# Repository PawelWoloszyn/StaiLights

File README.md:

Stairs is electronics and programming project of controlling stair lights (led strips attached to bottom side of each step) using arduino nano and tlc5940.
Project contains both electronic schematics and code needed to create such controller, mind that I'm neither professional electronics
circuit designer nor software developer therefore both code and schematics might be adjusted to benefit your own implication.

Right now the device is under development and will remain in this state until implemented in real which is going to allow it's
long term testing and proof it's reliability. In this moment it only serves presentation purpose.

How does it work???
Arduino Nano controlls two TLC5940 controllers which are basicaly 16 channel PWM controller (each chip). PWM signal is inverted and used to drive MOSFET tranzistors which are responsible for regulating the current running through led strips. In order to automate this device DS1307 RTC is used. Thanks to this, device will only be switched on within specified period of time which is calculated by Dusk2Dawn library, lights are triggered by two PIR sensors one upstairs and one downstairs but there are plenty enough spare pins on Arduino nano to use other type of sesnor. Project also allows to externaly regulate device's parameters using microswitch buttons and potentiometer. 

Questions that might bother you:

* What do you need for logical inverters?
- TLC5940 cannot be connected directly to MOSFETS in this project due to it's 0 based logic, of course they could be driven with inverted logic but because of the way tlc functions, you wouldn't be able to completely shut down the lights.

* On schematic you started connecting TLC pins starting from output 2 not 0 why?
- It's because I bought one chip from second hand with one pin missing. Therefore I skipped pin0 and pin1(missing).

Future improvements:
* Definitely chaging DS1307 to DS3231 in order to gain benefits of having alarm clock function in real time clock, which could later on be used to     wake up arduino from sleep mode.
* Reworking board design to decrease it's dimensions, would probably make a 2 sided SMD PCB.

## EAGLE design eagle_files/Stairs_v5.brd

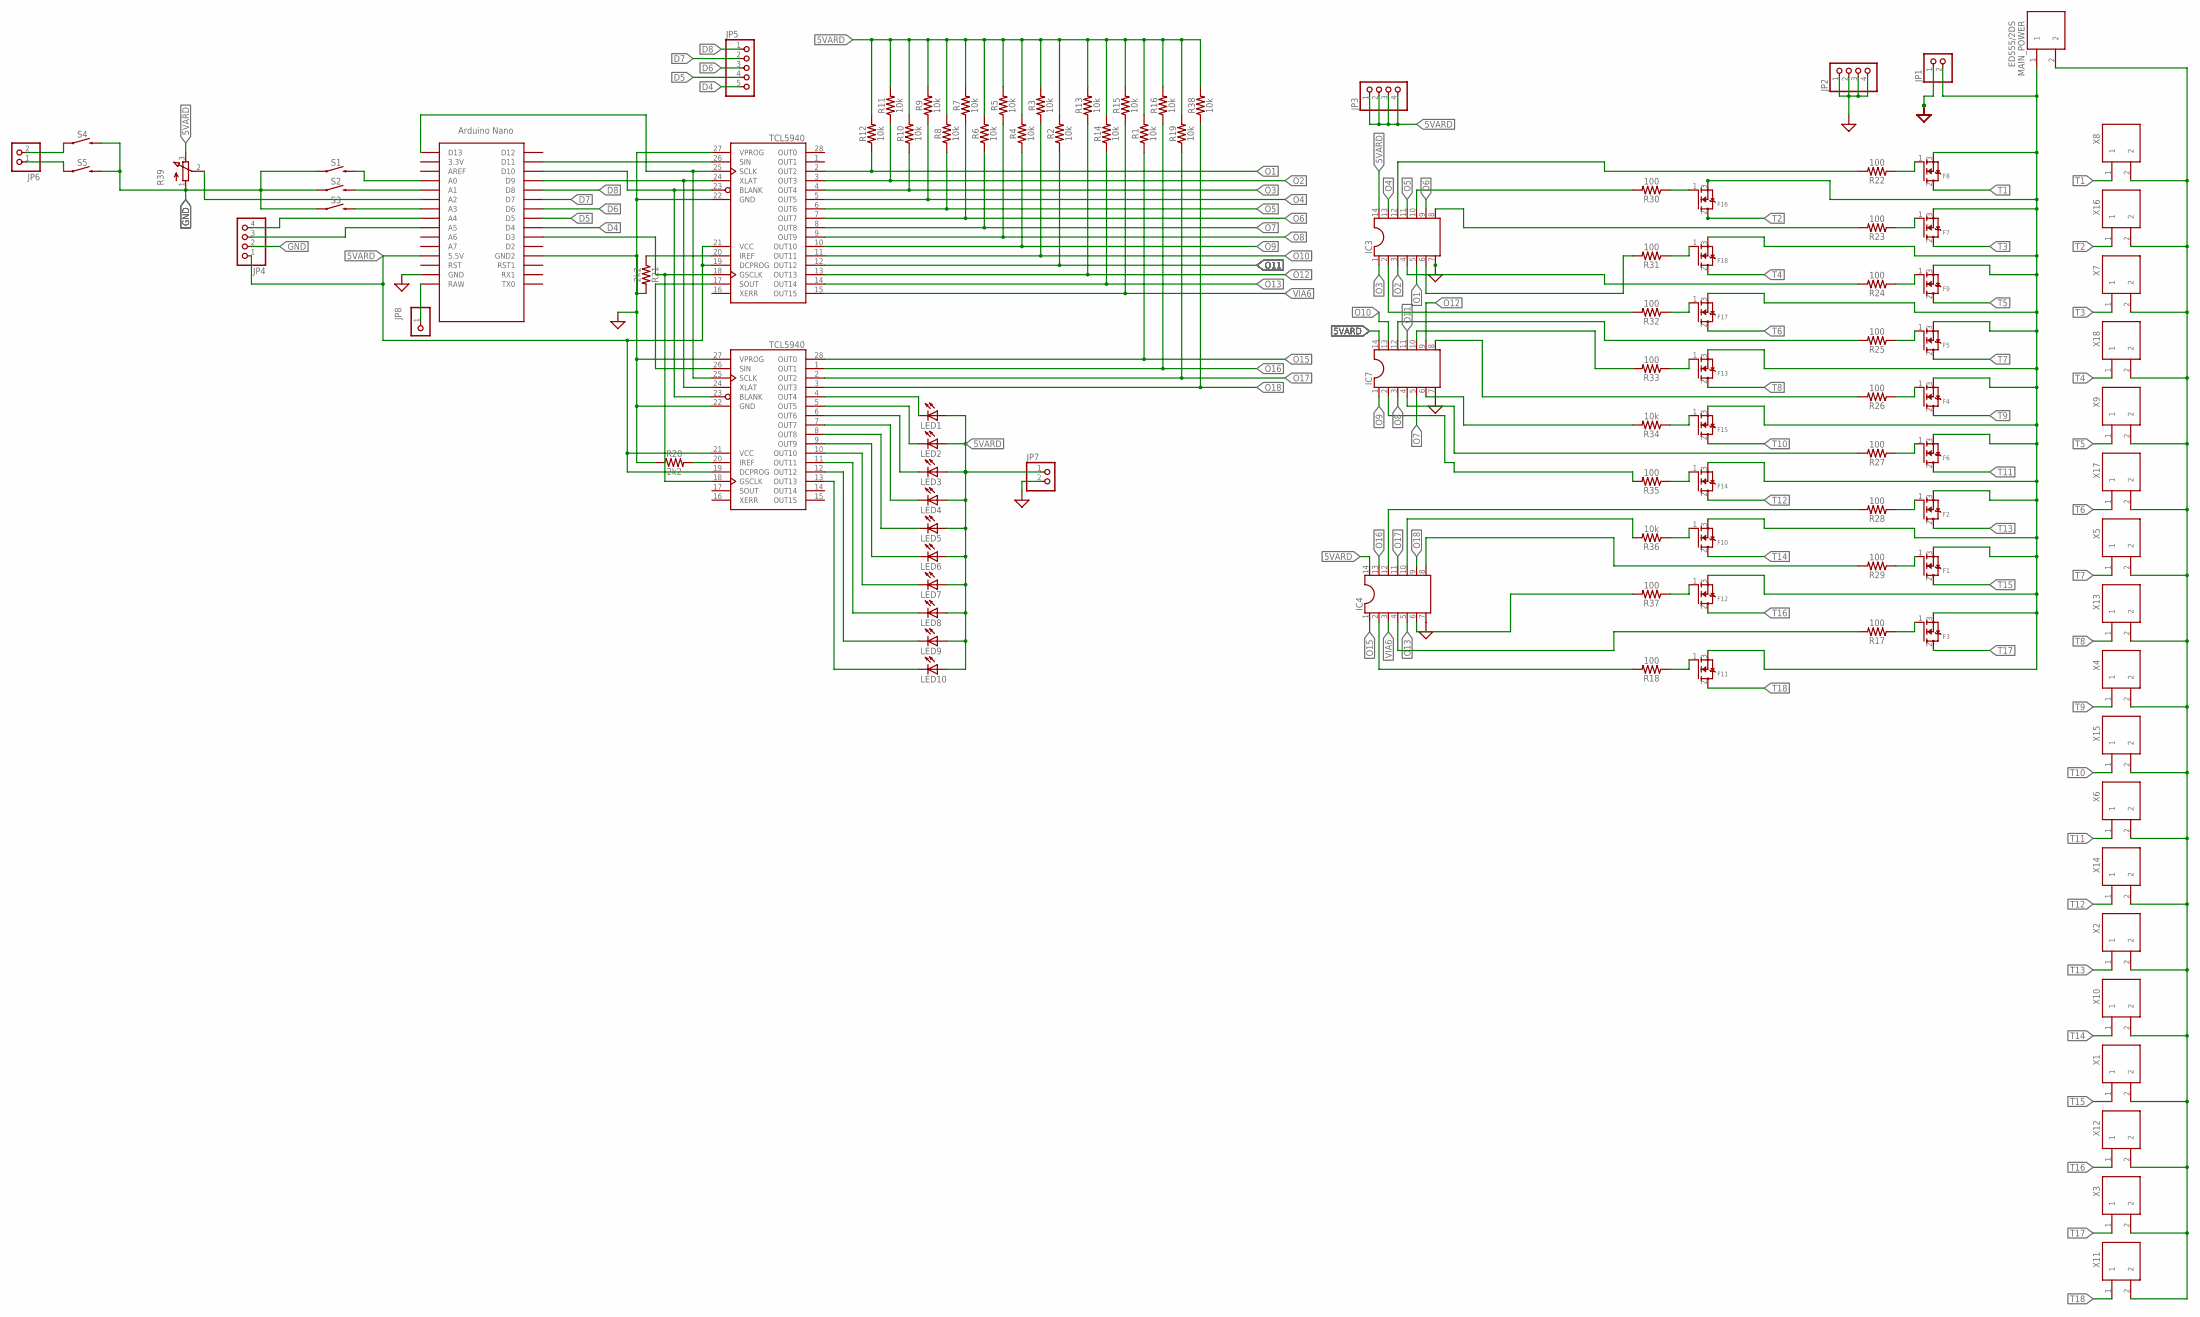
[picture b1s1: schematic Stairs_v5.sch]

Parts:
F1, F2, F3, F4, F5, F6, F7, F8, F9, F10, F11, F12, F13, F14, F15, F16, F17, F18: MOSFET-NGDS_TO220V; TO220V
IC1, IC2: TCL5940; DIP28
IC3, IC4, IC7: DIL14S; SOCKET-14
JP1, JP6, JP7: PINHD-1X2; 1X02
JP2, JP3, JP4: PINHD-1X4; 1X04
JP5: PINHD-1X5; 1X05
JP8: PINHD-1X1; 1X01
LED1, LED2, LED3, LED4, LED5, LED6, LED7, LED8, LED9, LED10: LEDSFH482; SFH482
MAIN_POWER: ED555/2DS
R1, R2, R3, R4, R5, R6, R7, R8, R9, R10, R11, R12, R13, R14, R15, R16, R19, R34, R36, R38: 10k; AXIAL-0.3-KIT
R17, R18, R22, R23, R24, R25, R26, R27, R28, R29, R30, R31, R32, R33, R35, R37: 100; AXIAL-0.3-KIT
R20, R21: 2k2; AXIAL-0.3-KIT
R39: 3RP/1610N
S1, S2, S3, S4, S5: MOMENTARY-SWITCH-SPST-PTH-6.0MM; TACTILE_SWITCH_PTH_6.0MM
U$1: NANO
X1, X2, X3, X4, X5, X6, X7, X8, X9, X10, X11, X12, X13, X14, X15, X16, X17, X18: ED555/2DS

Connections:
5VARD: IC1.19 (DCPROG), IC1.21 (VCC), IC2.19 (DCPROG), IC2.21 (VCC), IC3.14, IC4.14, IC7.14, JP3.1, JP3.2, JP3.3, JP3.4, JP4.1, JP7.1, LED1.A, LED2.A, LED3.A, LED4.A, LED5.A, LED6.A, LED7.A, LED8.A, LED9.A, LED10.A, R1.P$2 (2), R2.P$2 (2), R3.P$2 (2), R4.P$2 (2), R5.P$2 (2), R6.P$2 (2), R7.P$2 (2), R8.P$2 (2), R9.P$2 (2), R10.P$2 (2), R11.P$2 (2), R12.P$2 (2), R13.P$2 (2), R14.P$2 (2), R15.P$2 (2), R16.P$2 (2), R19.P$2 (2), R38.P$2 (2), R39.3 (E), U$1.5V (5.5V)
D4: JP5.5, U$1.D4
D5: JP5.4, U$1.D5
D6: JP5.3, U$1.D6
D7: JP5.2, U$1.D7
D8: JP5.1, U$1.D8
GND: IC1.22 (GND), IC1.27 (VPROG), IC2.22 (GND), IC2.27 (VPROG), IC3.7, IC4.7, IC7.7, JP1.1, JP2.1, JP2.2, JP2.3, JP2.4, JP4.2, JP7.2, R20.P$1 (1), R21.P$2 (2), R39.1 (A), S1.1, S2.1, S3.1, S4.3 (2), S5.3 (2), U$1.GND, U$1.GND1 (GND2)
unnamed: IC2.4 (OUT4), LED1.K (C)
unnamed: JP8.1, U$1.RAW
unnamed: IC1.25 (SCLK), IC2.25 (SCLK), U$1.D13
unnamed: IC1.24 (XLAT), IC2.24 (XLAT), U$1.D9
unnamed: IC2.5 (OUT5), LED2.K (C)
unnamed: JP6.2, S4.1
unnamed: S1.3 (2), U$1.A0
unnamed: IC1.17 (SOUT), IC2.26 (SIN)
unnamed: IC1.20 (IREF), R21.P$1 (1)
unnamed: IC2.20 (IREF), R20.P$2 (2)
unnamed: F7.1 (G), R23.P$1 (1)
unnamed: IC1.18 (GSCLK), IC2.18 (GSCLK), U$1.D3
unnamed: S2.3 (2), U$1.A1
unnamed: R39.2 (S), U$1.A2
unnamed: F9.1 (G), R24.P$1 (1)
unnamed: S3.3 (2), U$1.A3
unnamed: JP4.4, U$1.A4
unnamed: F5.1 (G), R25.P$1 (1)
unnamed: JP4.3, U$1.A5
unnamed: F4.1 (G), R26.P$1 (1)
unnamed: JP6.1, S5.1
unnamed: F8.1 (G), R22.P$1 (1)
unnamed: IC2.6 (OUT6), LED3.K (C)
unnamed: F6.1 (G), R27.P$1 (1)
unnamed: IC2.7 (OUT7), LED4.K (C)
unnamed: IC2.8 (OUT8), LED5.K (C)
unnamed: F2.1 (G), R28.P$1 (1)
unnamed: IC2.9 (OUT9), LED6.K (C)
unnamed: IC2.10 (OUT10), LED7.K (C)
unnamed: F1.1 (G), R29.P$1 (1)
unnamed: IC2.11 (OUT11), LED8.K (C)
unnamed: IC2.12 (OUT12), LED9.K (C)
unnamed: IC2.13 (OUT13), LED10.K (C)
unnamed: F16.1 (G), R30.P$1 (1)
unnamed: F18.1 (G), R31.P$1 (1)
unnamed: F17.1 (G), R32.P$1 (1)
unnamed: F13.1 (G), R33.P$1 (1)
unnamed: F15.1 (G), R34.P$1 (1)
unnamed: F14.1 (G), R35.P$1 (1)
unnamed: F10.1 (G), R36.P$1 (1)
unnamed: F12.1 (G), R37.P$1 (1)
unnamed: IC3.12, R22.P$2 (2)
unnamed: IC3.8, R23.P$2 (2)
unnamed: IC3.4, R24.P$2 (2)
unnamed: IC7.10, R33.P$2 (2)
unnamed: IC3.10, R30.P$2 (2)
unnamed: IC3.6, R31.P$2 (2)
unnamed: IC3.2, R32.P$2 (2)
unnamed: IC7.12, R25.P$2 (2)
unnamed: IC7.8, R26.P$2 (2)
unnamed: IC7.4, R27.P$2 (2)
unnamed: IC4.12, R28.P$2 (2)
unnamed: IC4.8, R29.P$2 (2)
unnamed: IC7.6, R34.P$2 (2)
unnamed: IC4.10, R36.P$2 (2)
unnamed: IC7.2, R35.P$2 (2)
unnamed: IC4.6, R37.P$2 (2)
unnamed: F3.1 (G), R17.P$1 (1)
unnamed: IC4.4, R17.P$2 (2)
unnamed: F11.1 (G), R18.P$1 (1)
unnamed: IC4.2, R18.P$2 (2)
O1: IC1.2 (OUT2), IC3.5, R12.P$1 (1)
O2: IC1.3 (OUT3), IC3.3, R11.P$1 (1)
O3: IC1.4 (OUT4), IC3.1, R10.P$1 (1)
O4: IC1.5 (OUT5), IC3.13, R9.P$1 (1)
O5: IC1.6 (OUT6), IC3.11, R8.P$1 (1)
O6: IC1.7 (OUT7), IC3.9, R7.P$1 (1)
O7: IC1.8 (OUT8), IC7.5, R6.P$1 (1)
O8: IC1.9 (OUT9), IC7.3, R5.P$1 (1)
O9: IC1.10 (OUT10), IC7.1, R4.P$1 (1)
O10: IC1.11 (OUT11), IC7.13, R3.P$1 (1)
O11: IC1.12 (OUT12), IC7.11, R2.P$1 (1)
O12: IC1.13 (OUT13), IC7.9, R13.P$1 (1)
O13: IC1.14 (OUT14), IC4.5, R14.P$1 (1)
O15: IC2.28 (OUT0), IC4.1, R1.P$1 (1)
O16: IC2.1 (OUT1), IC4.13, R16.P$1 (1)
O17: IC2.2 (OUT2), IC4.11, R19.P$1 (1)
O18: IC2.3 (OUT3), IC4.9, R38.P$1 (1)
POWER+: MAIN_POWER.2, X1.2, X2.2, X3.2, X4.2, X5.2, X6.2, X7.2, X8.2, X9.2, X10.2, X11.2, X12.2, X13.2, X14.2, X15.2, X16.2, X17.2, X18.2
POWER-: F1.3 (S), F2.3 (S), F3.3 (S), F4.3 (S), F5.3 (S), F6.3 (S), F7.3 (S), F8.3 (S), F9.3 (S), F10.3 (S), F11.3 (S), F12.3 (S), F13.3 (S), F14.3 (S), F15.3 (S), F16.3 (S), F17.3 (S), F18.3 (S), JP1.2, MAIN_POWER.1
T1: F8.2 (D), X8.1
T2: F16.2 (D), X16.1
T3: F7.2 (D), X7.1
T4: F18.2 (D), X18.1
T5: F9.2 (D), X9.1
T6: F17.2 (D), X17.1
T7: F5.2 (D), X5.1
T8: F13.2 (D), X13.1
T9: F4.2 (D), X4.1
T10: F15.2 (D), X15.1
T11: F6.2 (D), X6.1
T12: F14.2 (D), X14.1
T13: F2.2 (D), X2.1
T14: F10.2 (D), X10.1
T15: F1.2 (D), X1.1
T16: F12.2 (D), X12.1
T17: F3.2 (D), X3.1
T18: F11.2 (D), X11.1
VIA4: IC1.26 (SIN), U$1.D11
VIA6: IC1.15 (OUT15), IC4.3, R15.P$1 (1)
VIAXX: IC1.23 (BLANK), IC2.23 (BLANK), U$1.D10

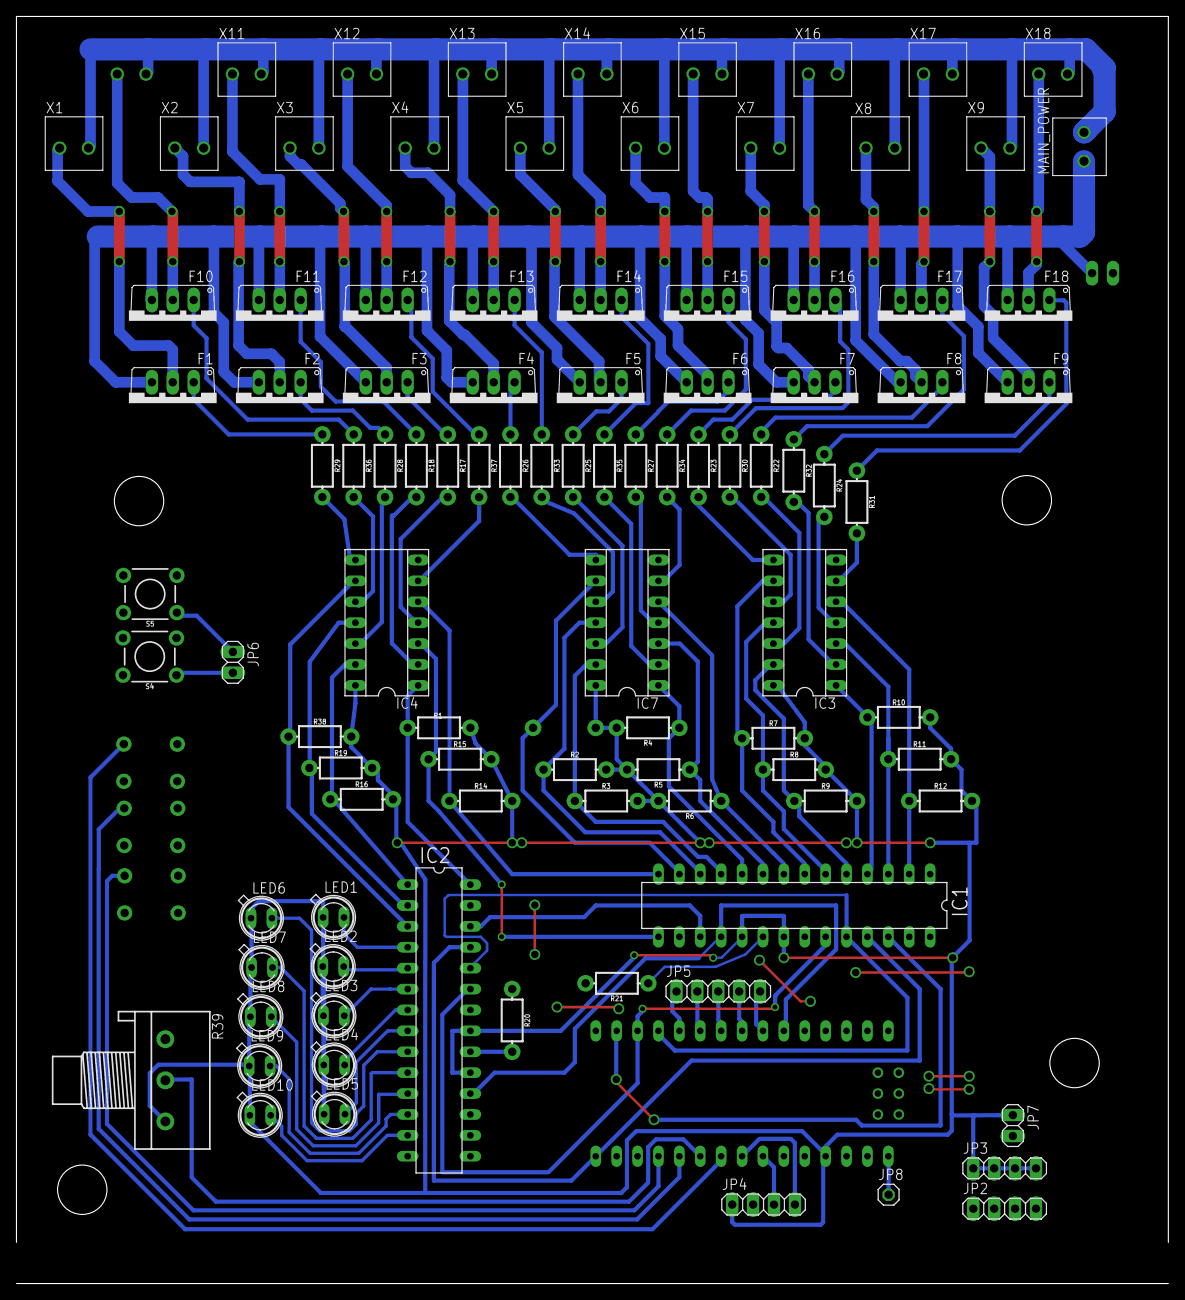
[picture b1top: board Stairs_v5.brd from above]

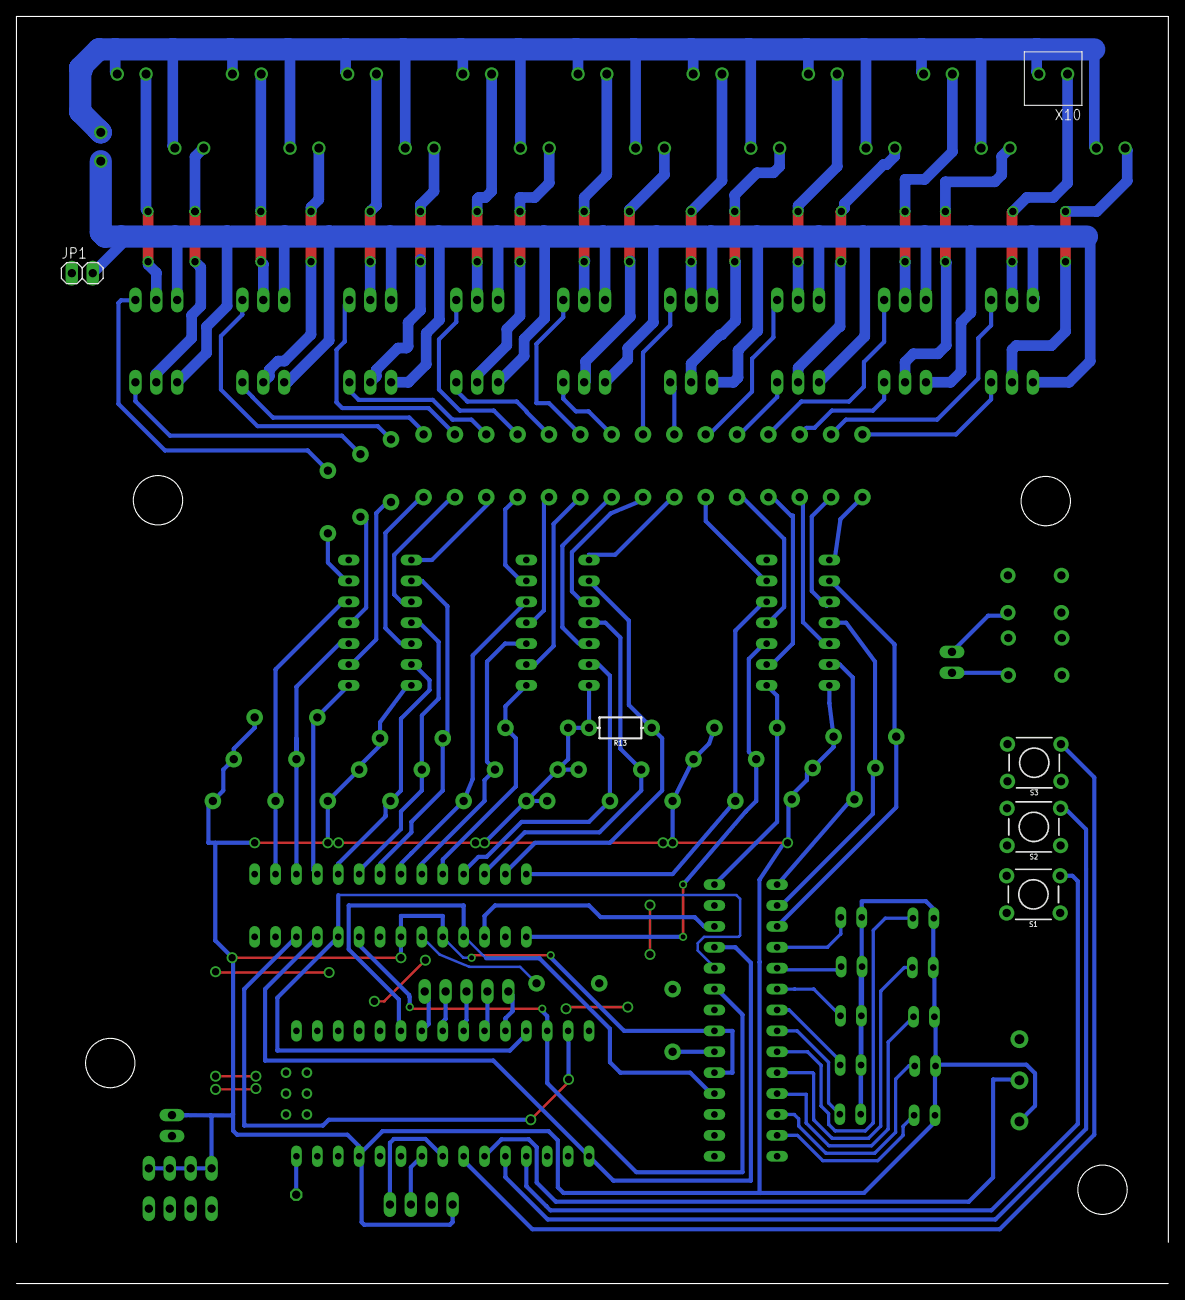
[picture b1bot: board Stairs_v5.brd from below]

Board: 2 copper layers, 140.0 x 154.0 mm, 105 parts (6 on the bottom side), 108 nets.

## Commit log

2018-12-20 first commit, fading:OK menu:testing required

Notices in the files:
parts and their libraries:
SparkFun-Resistors: Licensing: Creative Commons ShareAlike 4.0 International - https://creativecommons.org/licenses/by-sa/4.0
